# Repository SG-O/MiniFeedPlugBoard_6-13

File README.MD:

# Mainboard for automated SMT Feeder system #

## Documentation ##

You can find the manufacturing documentation [here.](https://github.com/SG-O/MiniFeedPlugBoard_6-13/tree/master/Doc)

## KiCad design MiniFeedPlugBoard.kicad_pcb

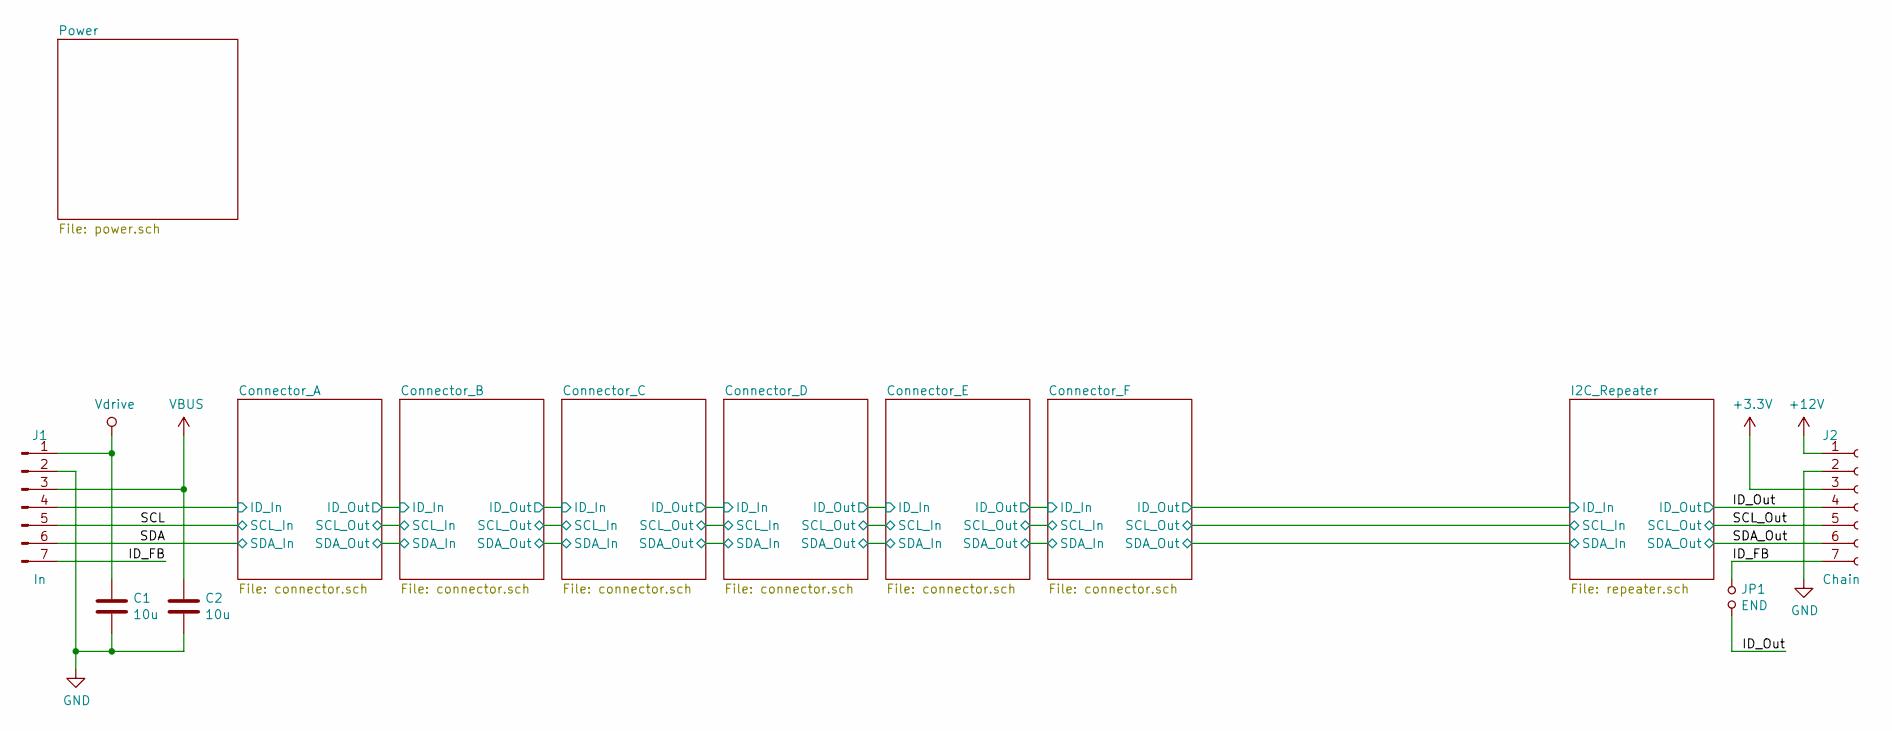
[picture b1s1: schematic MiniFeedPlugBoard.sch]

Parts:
C1, C2: 10u; C_1206_3216Metric; lcsc# C14860
J1: In; PinHeader_1x07_P2.54mm_Horizontal; lcsc# C376125
J2: Chain; PinSocket_1x07_P2.54mm_Horizontal; lcsc# C225515
JP1: END; PinHeader_1x02_P2.54mm_Horizontal; lcsc# C376120;C5305

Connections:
+3V3: J2.3; also elsewhere on the board
+12V: J2.1; also elsewhere on the board
/Connector_A/ID_In: J1.4; also elsewhere on the board
/ID_FB: J1.7, J2.7, JP1.1
/ID_Out: J2.4, JP1.2; also elsewhere on the board
/SCL: J1.5; also elsewhere on the board
/SCL_Out: J2.5; also elsewhere on the board
/SDA: J1.6; also elsewhere on the board
/SDA_Out: J2.6; also elsewhere on the board
GND: C1.1, C2.1, J1.2, J2.2; also elsewhere on the board
VBUS: C2.2, J1.3; also elsewhere on the board
Vdrive: C1.2, J1.1; also elsewhere on the board

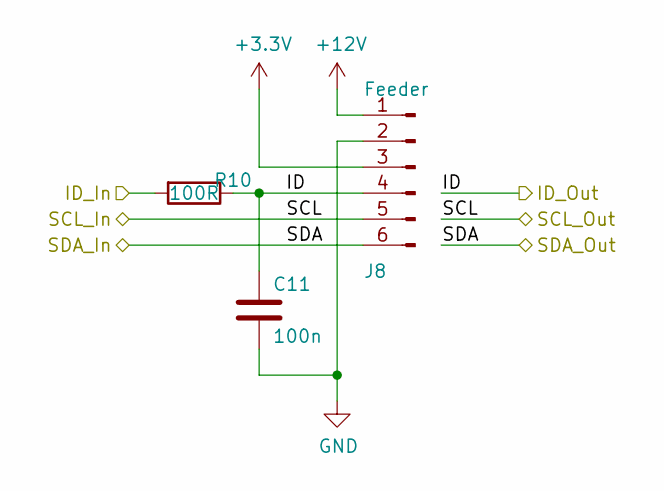
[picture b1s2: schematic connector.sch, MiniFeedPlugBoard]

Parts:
C3: 100n; C_0603_1608Metric; lcsc# C1591
J3: Feeder; PogoEdgeConnector
R1: 100R; R_0603_1608Metric; lcsc# C217683

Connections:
+3V3: J3.3; also elsewhere on the board
+12V: J3.1; also elsewhere on the board
/Connector_A/ID_In: R1.2; also elsewhere on the board
/Connector_B/ID_In: C3.2, J3.4, R1.1; also elsewhere on the board
/SCL: J3.5; also elsewhere on the board
/SDA: J3.6; also elsewhere on the board
GND: C3.1, J3.2; also elsewhere on the board

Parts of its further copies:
C7, C8, C9, C10, C11, C25, C26: 100n; C_0603_1608Metric; lcsc# C1591
J4, J5, J6, J7, J8, J10, J11: Feeder; PogoEdgeConnector
R6, R7, R8, R9, R10, R22, R23: 100R; R_0603_1608Metric; lcsc# C217683

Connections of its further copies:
+3V3: J4.3, J5.3, J6.3, J7.3, J8.3; also elsewhere on the board
+12V: J4.1, J5.1, J6.1, J7.1, J8.1; also elsewhere on the board
/Connector_B/ID_In: R6.2; also elsewhere on the board
/Connector_C/ID_In: C7.2, J4.4, R6.1, R7.2
/Connector_D/ID_In: C8.2, J5.4, R7.1, R8.2
/Connector_E/ID_In: C9.2, J6.4, R8.1, R9.2
/Connector_F/ID_In: C10.2, J7.4, R9.1, R10.2
/ID_Out: C11.2, J8.4, R10.1; also elsewhere on the board
/SCL: J4.5, J5.5, J6.5, J7.5, J8.5; also elsewhere on the board
/SDA: J4.6, J5.6, J6.6, J7.6, J8.6; also elsewhere on the board
GND: C7.1, C8.1, C9.1, C10.1, C11.1, J4.2, J5.2, J6.2, J7.2, J8.2; also elsewhere on the board

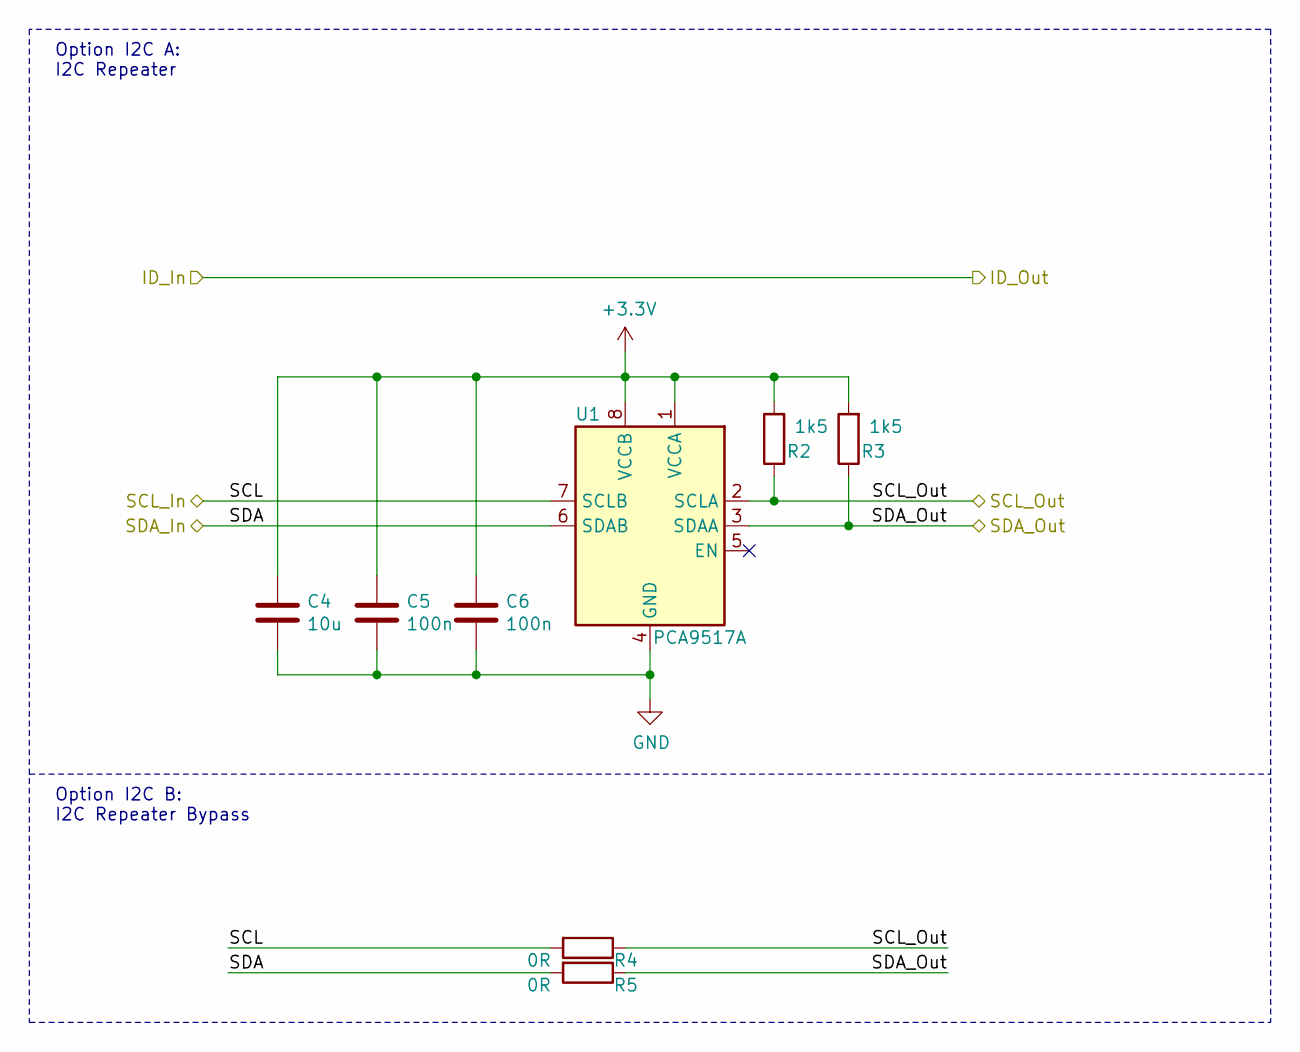
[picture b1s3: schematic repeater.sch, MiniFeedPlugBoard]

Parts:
C4: 10u; C_1206_3216Metric; lcsc# C14860
C5, C6: 100n; C_0603_1608Metric; lcsc# C1591
R2, R3: 1k5; R_0805_2012Metric; lcsc# C118217
R4, R5: 0R; R_0603_1608Metric; lcsc# C163836
U1: PCA9517A; TSSOP-8_3x3mm_P0.65mm; lcsc# C80799

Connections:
+3V3: C4.2, C5.2, C6.2, R2.2, R3.2, U1.1 (VCCA), U1.8 (VCCB); also elsewhere on the board
/SCL: R4.2, U1.7 (SCLB); also elsewhere on the board
/SCL_Out: R2.1, R4.1, U1.2 (SCLA); also elsewhere on the board
/SDA: R5.2, U1.6 (SDAB); also elsewhere on the board
/SDA_Out: R3.1, R5.1, U1.3 (SDAA); also elsewhere on the board
GND: C4.1, C5.1, C6.1, U1.4 (GND); also elsewhere on the board

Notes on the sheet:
Option I2C A: I2C Repeater
Option I2C B: I2C Repeater Bypass

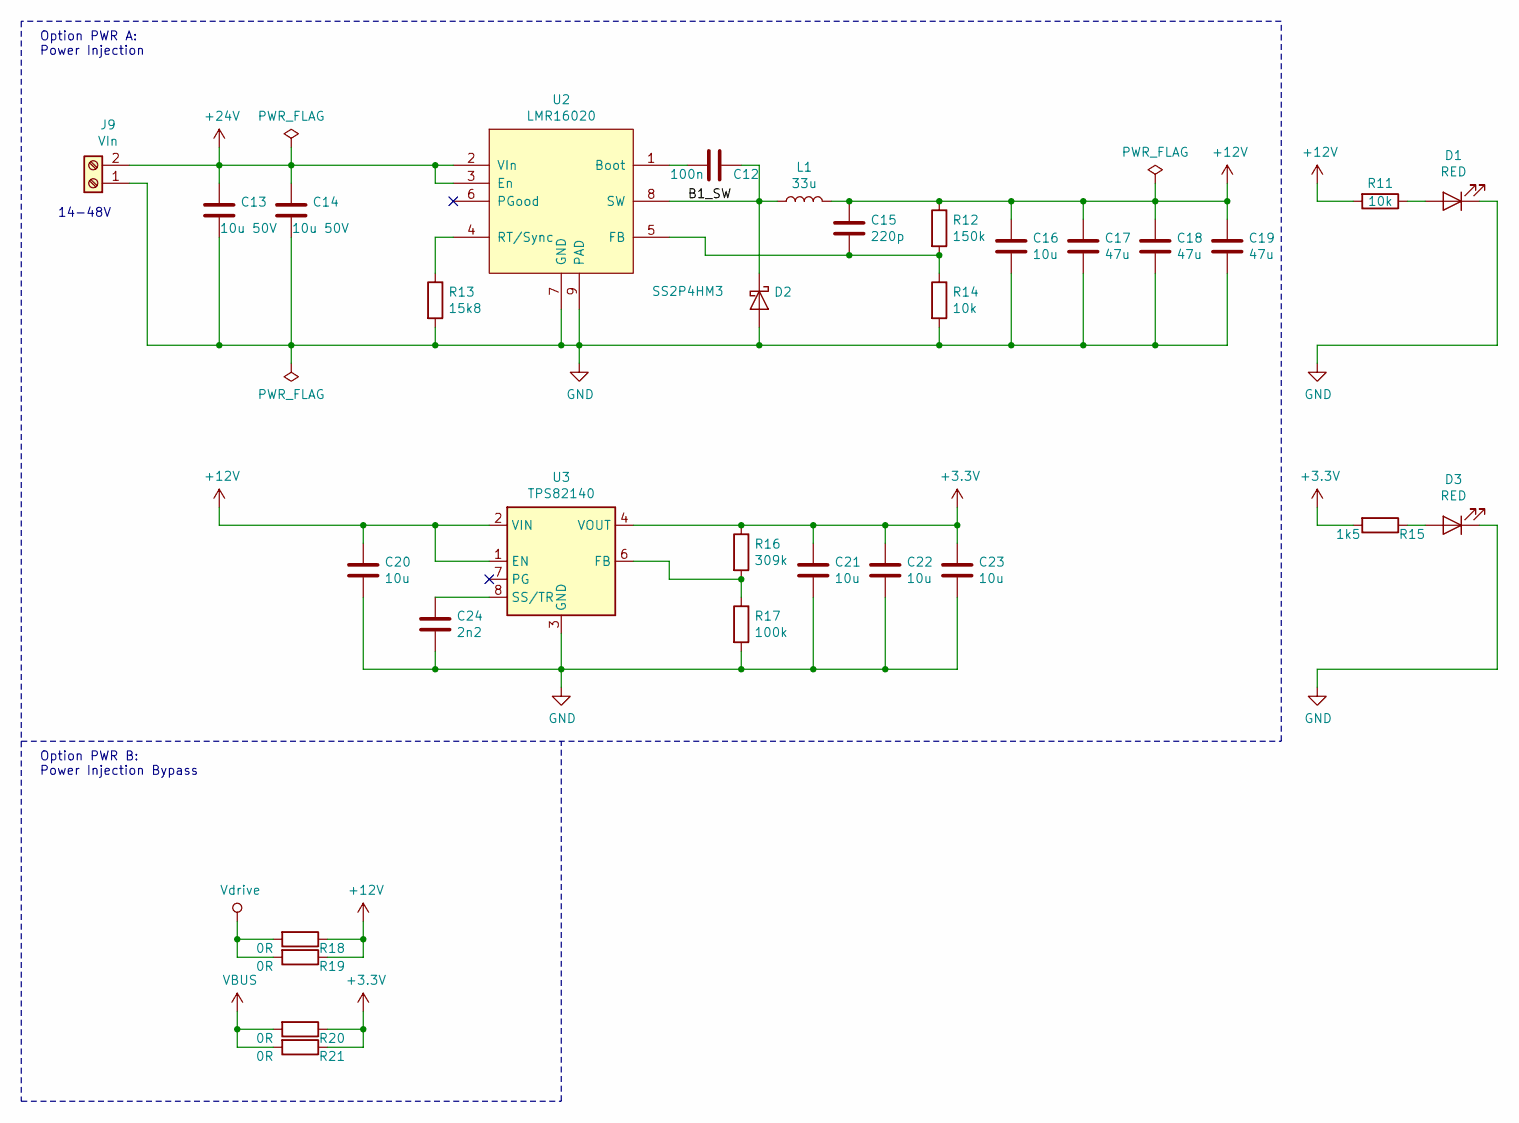
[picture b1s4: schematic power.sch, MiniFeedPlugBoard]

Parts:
C12: 100n; C_0603_1608Metric; lcsc# C1591
C13, C14: 10u 50V; C_1210_3225Metric; lcsc# C337485
C15: 220p; C_0603_1608Metric; lcsc# C27675
C16, C20, C21, C22, C23: 10u; C_1206_3216Metric; lcsc# C14860
C17, C18, C19: 47u; C_2220_5650Metric; lcsc# C342293
C24: 2n2; C_0603_1608Metric; lcsc# C16033
D1, D3: RED; LED_0603_1608Metric; lcsc# C118330
D2: SS2P4HM3; DO-220AA; lcsc# C467996
J9: VIn; PhoenixContact_MC_1,5_2-G-3.81_1x02_P3.81mm_Horizontal; lcsc# C8387;C8466
L1: 33u; Inductor10x10mm; lcsc# C253612
R11, R14: 10k; R_0603_1608Metric; lcsc# C128781
R12: 150k; R_0603_1608Metric; lcsc# C311920
R13: 15k8; R_0603_1608Metric; lcsc# C149924
R15: 1k5; R_0805_2012Metric; lcsc# C118217
R16: 309k; R_0603_1608Metric; lcsc# C56054
R17: 100k; R_0603_1608Metric; lcsc# C133733
R18, R19, R20, R21: 0R; R_0603_1608Metric; lcsc# C163836
U2: LMR16020; SOIC-8-1EP_3.9x4.9mm_P1.27mm_EP2.41x3.3mm_ThermalVias; lcsc# C190006
U3: TPS82140; Texas_SIL0008D_MicroSiP-8-1EP_2.8x3mm_P0.65mm_EP1.1x1.9mm_T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; lcsc# C544385

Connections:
+3V3: C21.1, C22.1, C23.1, R15.2, R16.1, R20.1, R21.1, U3.4 (VOUT), U3.5 (VOUT); also elsewhere on the board
+12V: C15.1, C16.1, C17.1, C18.1, C19.1, C20.1, L1.2, R11.2, R12.1, R18.1, R19.1, U3.1 (EN), U3.2 (VIN); also elsewhere on the board
+24V: C13.1, C14.1, J9.2, U2.2 (VIn), U2.3 (En)
/Power/B1_SW: C12.1, D2.1 (K), L1.1, U2.8 (SW)
GND: C13.2, C14.2, C16.2, C17.2, C18.2, C19.2, C20.2, C21.2, C22.2, C23.2, C24.2, D1.1 (K), D2.2 (A), D3.1 (K), J9.1, R13.2, R14.2, R17.2, U2.7 (GND), U2.9 (PAD), U3.3 (GND), U3.9 (GND); also elsewhere on the board
unnamed: C12.2, U2.1 (Boot)
unnamed: C15.2, R12.2, R14.1, U2.5 (FB)
unnamed: C24.1, U3.8 (SS/TR)
unnamed: D1.2 (A), R11.1
unnamed: D3.2 (A), R15.1
unnamed: R13.1, U2.4 (RT/Sync)
unnamed: R16.2, R17.1, U3.6 (FB)
VBUS: R20.2, R21.2; also elsewhere on the board
Vdrive: R18.2, R19.2; also elsewhere on the board

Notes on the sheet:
14-48V
Option PWR B: Power Injection Bypass
Option PWR A: Power Injection

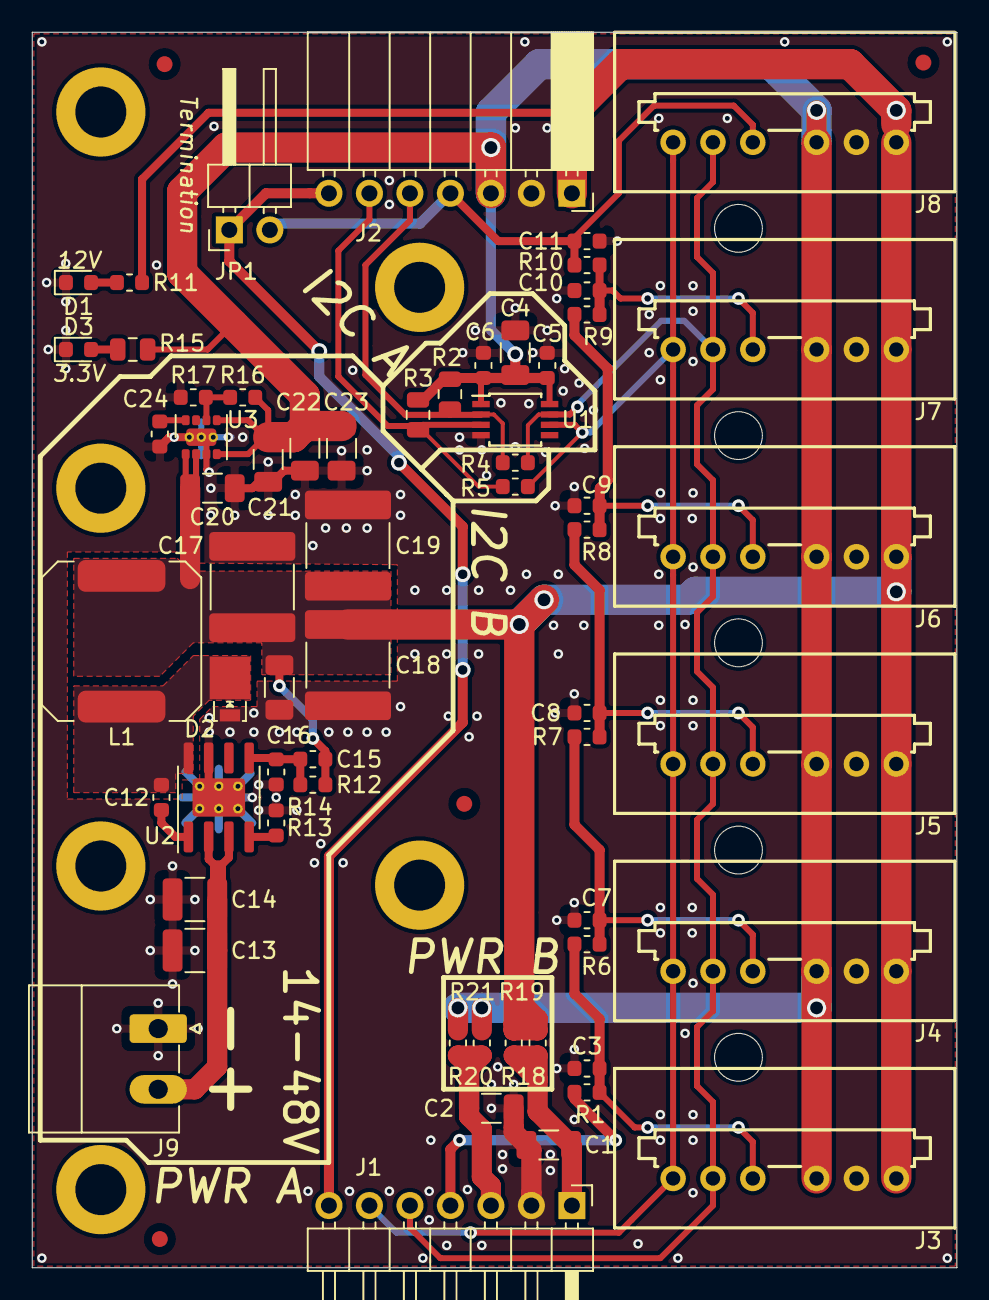
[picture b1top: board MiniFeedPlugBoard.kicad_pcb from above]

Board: 2 copper layers, 58.0 x 77.5 mm, 66 parts (0 on the bottom side), 26 nets.

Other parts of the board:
Fid1, Fid2, Fid3, Fid4: Fiducial_1mm_Mask2mm

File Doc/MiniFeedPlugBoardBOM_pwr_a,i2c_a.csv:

Component,Description,Part,References,Value,Footprint,Quantity Per PCB,Datasheet,lcsc#,manf#
1,Unpolarized capacitor,C,C3 C5 C6 C7 C8 C9 C10 C11 C12,100n,C_0603_1608Metric,9,~,C1591,CL10B104KB8NNNC
2,Unpolarized capacitor,C,C1 C2 C4 C16 C20 C21 C22 C23,10u,C_1206_3216Metric,8,~,C14860,CL31B106KAHNNNE
3,Unpolarized capacitor,C,C13 C14,10u 50V,C_1210_3225Metric,2,~,C337485,UMK325AB7106KM-P
4,Unpolarized capacitor,C,C15,220p,C_0603_1608Metric,1,~,C27675,CL10C221JB8NNNC
5,Unpolarized capacitor,C,C24,2n2,C_0603_1608Metric,1,~,C16033,CL10B222KB8NNNC
6,Unpolarized capacitor,C,C17 C18 C19,47u,C_2220_5650Metric,3,~,C342293,CGA9N3X7R1C476MT0Y0N
7,Light emitting diode,LED,D1 D3,RED,LED_0603_1608Metric,2,~,C118330,D-060306R1/SS2/L
8,Schottky diode,D_Schottky,D2,SS2P4HM3,DO-220AA,1,~,C467996,SS2P4HM3/84A
9,"Generic connector, single row, 01x07, script generated (kicad-library-utils/schlib/autogen/connector/)",Conn_01x07_Female,J2,Chain,PinSocket_1x07_P2.54mm_Horizontal,1,~,C225515,A2541HWR-7P
10,"Generic connector, single row, 01x06, script generated (kicad-library-utils/schlib/autogen/connector/)",Conn_01x06_Male,J3 J4 J5 J6 J7 J8,Feeder,PogoEdgeConnector,6,~,,
11,"Generic connector, single row, 01x07, script generated (kicad-library-utils/schlib/autogen/connector/)",Conn_01x07_Male,J1,In,PinHeader_1x07_P2.54mm_Horizontal,1,~,C376125,MTB125-1107R1
12,"Generic screw terminal, single row, 01x02, script generated (kicad-library-utils/schlib/autogen/connector/)",Screw_Terminal_01x02,J9,VIn,"PhoenixContact_MC_1,5_2-G-3.81_1x02_P3.81mm_Horizontal",1,~,C8387;C8466,WJ15EDGRC-3.81-2P;WJ15EDGK-3.81-2P
13,"Jumper, normally open, small symbol",Jumper_NO_Small,JP1,END,PinHeader_1x02_P2.54mm_Horizontal,1,~,C376120;C5305,MTB125-1102R1;C5305
14,Inductor,L,L1,33u,Inductor10x10mm,1,~,C253612,ABG10A50M330
15,Resistor,R,R1 R6 R7 R8 R9 R10,100R,R_0603_1608Metric,6,~,C217683,ARG03FTC1000
16,Resistor,R,R17,100k,R_0603_1608Metric,1,~,C133733,TC0325F1003T5E
17,Resistor,R,R11 R14,10k,R_0603_1608Metric,2,~,C128781,TC0325F1002T5E
18,Resistor,R,R12,150k,R_0603_1608Metric,1,~,C311920,ARG03DTC1503
19,Resistor,R,R13,15k8,R_0603_1608Metric,1,~,C149924,TR0603B15K8P0525Z
20,Resistor,R,R2 R3 R15,1k5,R_0805_2012Metric,3,~,C118217,TC0525F1501T5E
21,Resistor,R,R16,309k,R_0603_1608Metric,1,~,C56054,TC0325B3093T5E
22,,LMR16020,U2,LMR16020,SOIC-8-1EP_3.9x4.9mm_P1.27mm_EP2.41x3.3mm_ThermalVias,1,https://www.ti.com/lit/ds/symlink/lmr16020.pdf?ts=1605917167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,C190006,LMR16020PDDAR
23,"Level-Translating I2C Bus Buffer/Repeater 3.3mA Current Source, VSSOP-8",TCA9803,U1,PCA9517A,TSSOP-8_3x3mm_P0.65mm,1,https://www.nxp.com/docs/en/data-sheet/PCA9517A.pdf,C80799,PCA9517ADP
24,"17V Input 2A Step-Down Converter MicroSiP Module with Integrated Inductor, μSiL-8",TPS82140,U3,TPS82140,Texas_SIL0008D_MicroSiP-8-1EP_2.8x3mm_P0.65mm_EP1.1x1.9mm_ThermalVias,1,http://www.ti.com/lit/ds/symlink/tps82140.pdf,C544385,TPS82140SILR
,,,,,,,,,
,,,,,,,,,
,,,,,,,,,
,,,,,,,,,
,,,,,,,,,
Component Groups:,25,,,,,,,,
Component Count:,62,,,,,,,,
Fitted Components:,56,,,,,,,,
Number of PCBs:,1,,,,,,,,
Total components:,56,,,,,,,,
Schematic Version:,,,,,,,,,
Schematic Date:,,,,,,,,,
PCB Variant:,pwr_a + i2c_a,,,,,,,,
BoM Date:,07.02.2021 0:04:15,,,,,,,,
Schematic Source:,MiniFeedPlugBoard.sch,,,,,,,,
KiCad Version:,Eeschema (5.1.5)-3,,,,,,,,

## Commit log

2021-02-06 Added CAD files Added position files Fixed drill size for two footprints

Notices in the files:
MiniFeedPlugBoard.kicad_pcb:
©CC BY 4.0
